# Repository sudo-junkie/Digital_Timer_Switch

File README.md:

# Digital_Timer_Switch

KiCad 7 design files (schematic, PCB, BOM, gerbers) for ATMEGA328P-based timer switch

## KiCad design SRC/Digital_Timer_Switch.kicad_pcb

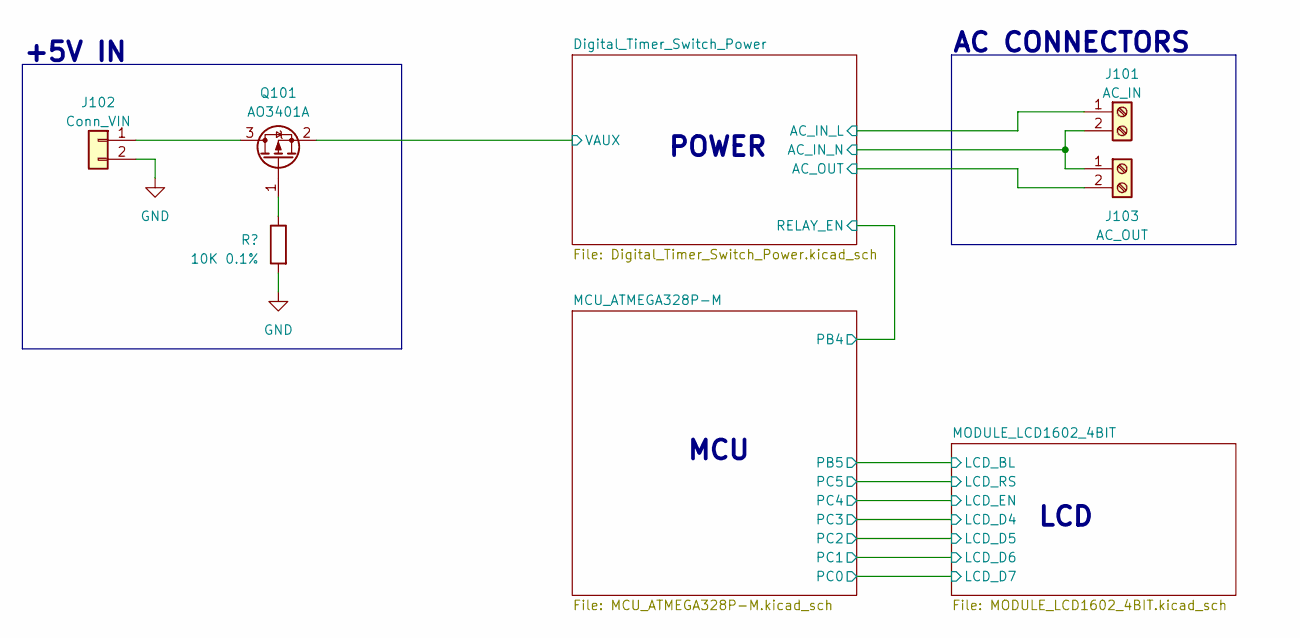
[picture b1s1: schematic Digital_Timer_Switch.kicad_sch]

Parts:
J101: AC_IN; TerminalBlock_Phoenix_MKDS-1,5-2-5.08_1x02_P5.08mm_Horizont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; MPN DB128V-5.08-2P-GN-S; LCSC PART# C2915639
J102: Conn_VIN; JST_XH_S2B-XH-A_1x02_P2.50mm_Horizontal; MPN S2B-XH-A-1(LF)(SN); LCSC PART# C163035
J103: AC_OUT; TerminalBlock_Phoenix_MKDS-1,5-2-5.08_1x02_P5.08mm_Horizont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; MPN DB128V-5.08-2P-GN-S; LCSC PART# C2915639
Q101: AO3401A; SOT-23; MPN AO3401; LCSC PART# C727156
R101: 10K 0.1%; R_0603_1608Metric; MPN RT0603BRD0710KL; LCSC PART# C95204

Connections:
/Digital_Timer_Switch_Power/AC_IN_L: J101.1; also elsewhere on the board
/Digital_Timer_Switch_Power/AC_IN_N: J101.2, J103.1; also elsewhere on the board
/Digital_Timer_Switch_Power/AC_OUT: J103.2; also elsewhere on the board
/Digital_Timer_Switch_Power/VAUX: Q101.2 (S); also elsewhere on the board
GND: J102.2, R101.2; also elsewhere on the board
unnamed: J102.1, Q101.3 (D)
unnamed: Q101.1 (G), R101.1

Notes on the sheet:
POWER
AC CONNECTORS
LCD
+5V IN
MCU

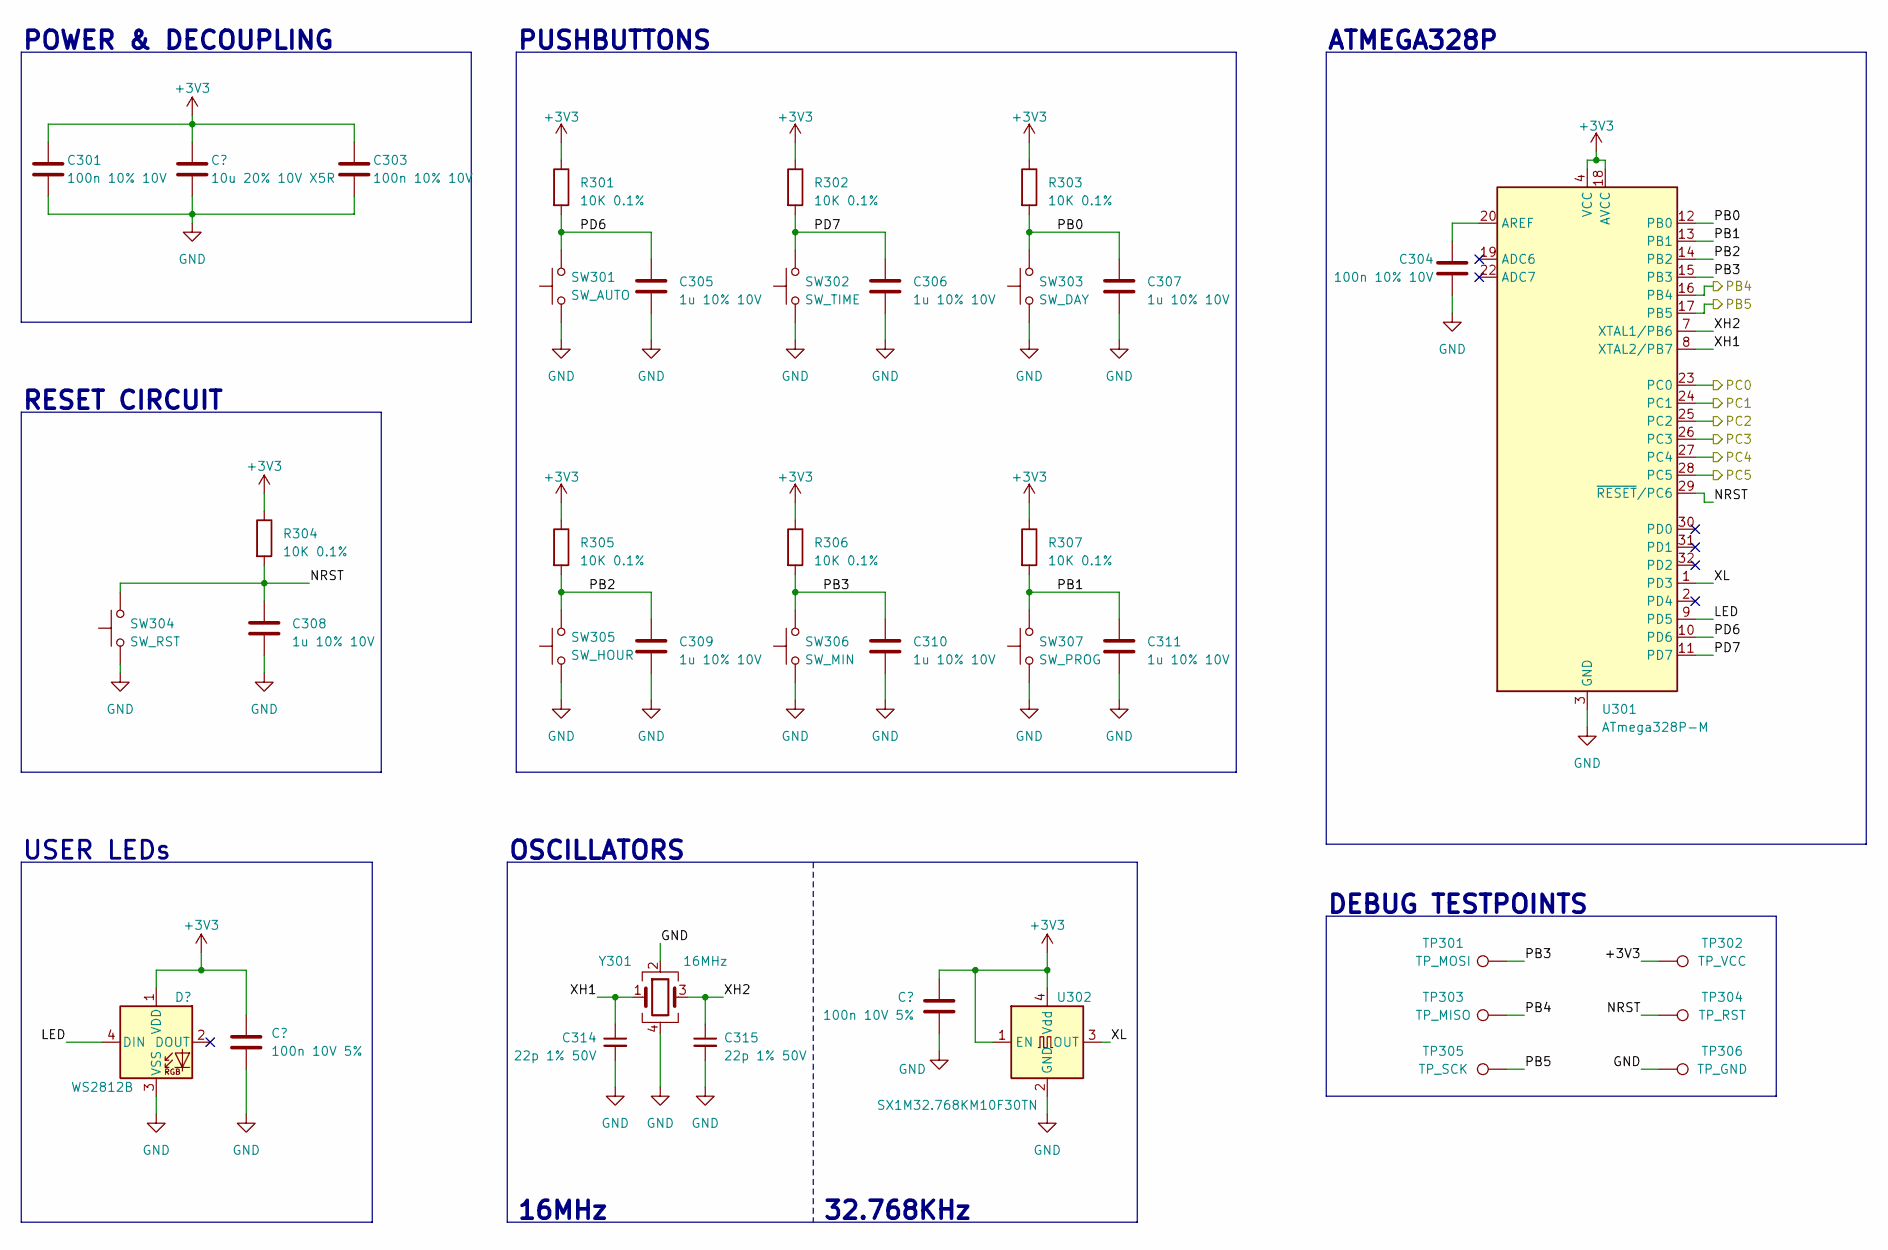
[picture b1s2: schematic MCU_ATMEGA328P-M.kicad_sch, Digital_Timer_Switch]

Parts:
C301, C303, C304: 100n 10% 10V; C_0603_1608Metric; MPN CC0603KRX7R6BB104; LCSC PART# C519438
C302: 10u 20% 10V X5R; C_0402_1005Metric; MPN CL05A106MP5NUNC; LCSC PART# C315248
C305, C306, C307, C308, C309, C310, C311: 1u 10% 10V; C_0603_1608Metric; MPN CC0603KRX7R6BB105; LCSC PART# C113807
C312, C313: 100n 10V 5%; C_0402_1005Metric; MPN CC0402JRX7R6BB104; LCSC PART# C527001
C314, C315: 22p 1% 50V; C_0603_1608Metric; MPN CC0603FRNPO9BN220; LCSC PART# C326840
D301: WS2812B; LED_WS2812B-2020_PLCC4_2.0x2.0mm; MPN XL-2020RGBC-WS2812B; LCSC PART# C5349955
R301, R302, R303, R304, R305, R306, R307: 10K 0.1%; R_0603_1608Metric; MPN RT0603BRD0710KL; LCSC PART# C95204
SW301: SW_AUTO; SW_SPST_Omron_B3FS-105xP; MPN TS-1095TS-B2C2-D2; LCSC PART# C5148360
SW302: SW_TIME; SW_SPST_Omron_B3FS-105xP; MPN TS-1095TS-B2C2-D2; LCSC PART# C5148360
SW303: SW_DAY; SW_SPST_Omron_B3FS-105xP; MPN TS-1095TS-B2C2-D2; LCSC PART# C5148360
SW304: SW_RST; SW_SPST_B3U-1000P; MPN B3U-1000P; LCSC PART# C231329
SW305: SW_HOUR; SW_SPST_Omron_B3FS-105xP; MPN TS-1095TS-B2C2-D2; LCSC PART# C5148360
SW306: SW_MIN; SW_SPST_Omron_B3FS-105xP; MPN TS-1095TS-B2C2-D2; LCSC PART# C5148360
SW307: SW_PROG; SW_SPST_Omron_B3FS-105xP; MPN TS-1095TS-B2C2-D2; LCSC PART# C5148360
TP301: TP_MOSI; TestPoint_Pad_D1.5mm
TP302: TP_VCC; TestPoint_Pad_D1.5mm
TP303: TP_MISO; TestPoint_Pad_D1.5mm
TP304: TP_RST; TestPoint_Pad_D1.5mm
TP305: TP_SCK; TestPoint_Pad_D1.5mm
TP306: TP_GND; TestPoint_Pad_D1.5mm
U301: ATmega328P-M; QFN-32-1EP_5x5mm_P0.5mm_EP3.1x3.1mm; MPN ATMEGA328P-MUR; LCSC PART# C2651951
U302: SX1M32.768KM10F30TN; Crystal_SMD_2016-4Pin_2.0x1.6mm; MPN SX1M32.768KM10F30TNN; LCSC PART# C2901615
Y301: 16MHz; Crystal_SMD_2016-4Pin_2.0x1.6mm; MPN TJ2116000UYGBC; LCSC PART# C2149179

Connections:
+3V3: C301.1, C302.1, C303.1, C312.1, C313.1, D301.1 (VDD), R301.1, R302.1, R303.1, R304.1, R305.1, R306.1, R307.1, TP302.1, U301.4 (VCC), U301.6 (VCC), U301.18 (AVCC), U302.1 (EN), U302.4 (Vdd); also elsewhere on the board
/MCU_ATMEGA328P-M/LED: D301.4 (DIN), U301.9 (PD5)
/MCU_ATMEGA328P-M/NRST: C308.1, R304.2, SW304.2, TP304.1, U301.29 (~RESET/PC6)
/MCU_ATMEGA328P-M/PB0: C307.1, R303.2, SW303.2, U301.12 (PB0)
/MCU_ATMEGA328P-M/PB1: C311.1, R307.2, SW307.2, U301.13 (PB1)
/MCU_ATMEGA328P-M/PB2: C309.1, R305.2, SW305.2, U301.14 (PB2)
/MCU_ATMEGA328P-M/PB3: C310.1, R306.2, SW306.2, TP301.1, U301.15 (PB3)
/MCU_ATMEGA328P-M/PB4: TP303.1, U301.16 (PB4); also elsewhere on the board
/MCU_ATMEGA328P-M/PB5: TP305.1, U301.17 (PB5); also elsewhere on the board
/MCU_ATMEGA328P-M/PC0: U301.23 (PC0); also elsewhere on the board
/MCU_ATMEGA328P-M/PC1: U301.24 (PC1); also elsewhere on the board
/MCU_ATMEGA328P-M/PC2: U301.25 (PC2); also elsewhere on the board
/MCU_ATMEGA328P-M/PC3: U301.26 (PC3); also elsewhere on the board
/MCU_ATMEGA328P-M/PC4: U301.27 (PC4); also elsewhere on the board
/MCU_ATMEGA328P-M/PC5: U301.28 (PC5); also elsewhere on the board
/MCU_ATMEGA328P-M/PD6: C305.1, R301.2, SW301.2, U301.10 (PD6)
/MCU_ATMEGA328P-M/PD7: C306.1, R302.2, SW302.2, U301.11 (PD7)
/MCU_ATMEGA328P-M/XH1: C314.1, U301.8 (XTAL2/PB7), Y301.1
/MCU_ATMEGA328P-M/XH2: C315.1, U301.7 (XTAL1/PB6), Y301.3
/MCU_ATMEGA328P-M/XL: U301.1 (PD3), U302.3 (OUT)
GND: C301.2, C302.2, C303.2, C304.2, C305.2, C306.2, C307.2, C308.2, C309.2, C310.2, C311.2, C312.2, C313.2, C314.2, C315.2, D301.3 (VSS), SW301.1, SW302.1, SW303.1, SW304.1, SW305.1, SW306.1, SW307.1, TP306.1, U301.3 (GND), U301.5 (GND), U301.21 (GND), U301.33 (GND), U302.2 (GND), Y301.2, Y301.4; also elsewhere on the board
unnamed: C304.1, U301.20 (AREF)

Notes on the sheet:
32.768KHz
ATMEGA328P
PUSHBUTTONS
16MHz
RESET CIRCUIT
OSCILLATORS
USER LEDs
POWER & DECOUPLING
DEBUG TESTPOINTS

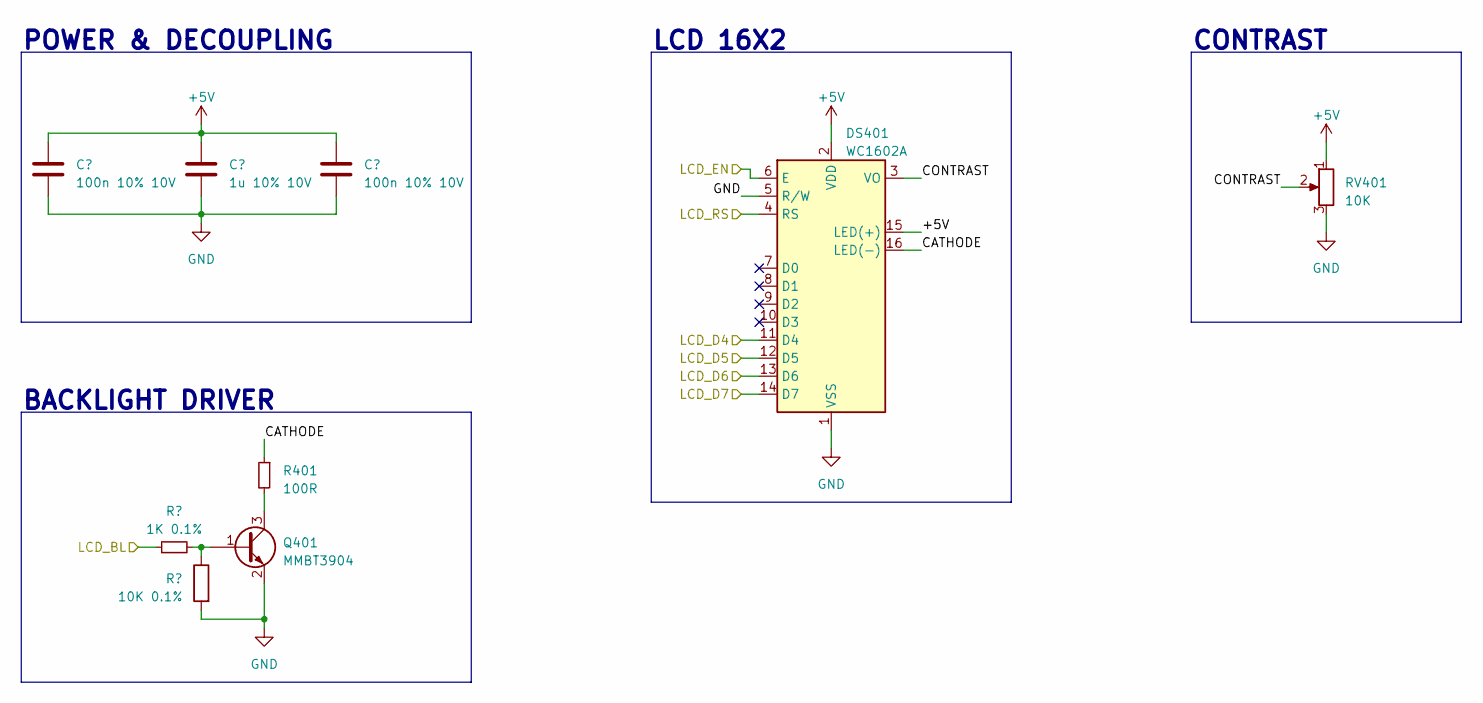
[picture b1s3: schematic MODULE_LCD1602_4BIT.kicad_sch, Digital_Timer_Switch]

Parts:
C401, C403: 100n 10% 10V; C_0603_1608Metric; MPN CC0603KRX7R6BB104; LCSC PART# C519438
C402: 1u 10% 10V; C_0603_1608Metric; MPN CC0603KRX7R6BB105; LCSC PART# C113807
DS401: WC1602A
Q401: MMBT3904; SOT-23; MPN MMBT3904; LCSC PART# C84104
R401: 100R; R_0603_1608Metric; MPN RC0603FR-07100RL; LCSC PART# C105588
R402: 1K 0.1%; R_0402_1005Metric; MPN ARG02BTC1001; LCSC PART# C2984405
R403: 10K 0.1%; R_0603_1608Metric; MPN RT0603BRD0710KL; LCSC PART# C95204
RV401: 10K; Potentiometer_Bourns_3314J_Vertical; MPN 3314J-1-103E; LCSC PART# C36376

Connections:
+5V: C401.1, C402.1, C403.1, DS401.2 (VDD), DS401.15 (LED(+)), RV401.1; also elsewhere on the board
/MCU_ATMEGA328P-M/PB5: R402.1; also elsewhere on the board
/MCU_ATMEGA328P-M/PC0: DS401.14 (D7); also elsewhere on the board
/MCU_ATMEGA328P-M/PC1: DS401.13 (D6); also elsewhere on the board
/MCU_ATMEGA328P-M/PC2: DS401.12 (D5); also elsewhere on the board
/MCU_ATMEGA328P-M/PC3: DS401.11 (D4); also elsewhere on the board
/MCU_ATMEGA328P-M/PC4: DS401.6 (E); also elsewhere on the board
/MCU_ATMEGA328P-M/PC5: DS401.4 (RS); also elsewhere on the board
/MODULE_LCD1602_4BIT/CATHODE: DS401.16 (LED(-)), R401.1
/MODULE_LCD1602_4BIT/CONTRAST: DS401.3 (VO), RV401.2
GND: C401.2, C402.2, C403.2, DS401.1 (VSS), DS401.5 (R/W), Q401.2 (E), R403.2, RV401.3; also elsewhere on the board
unnamed: Q401.1 (B), R402.2, R403.1
unnamed: Q401.3 (C), R401.2

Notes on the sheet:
POWER & DECOUPLING
CONTRAST
BACKLIGHT DRIVER
LCD 16X2

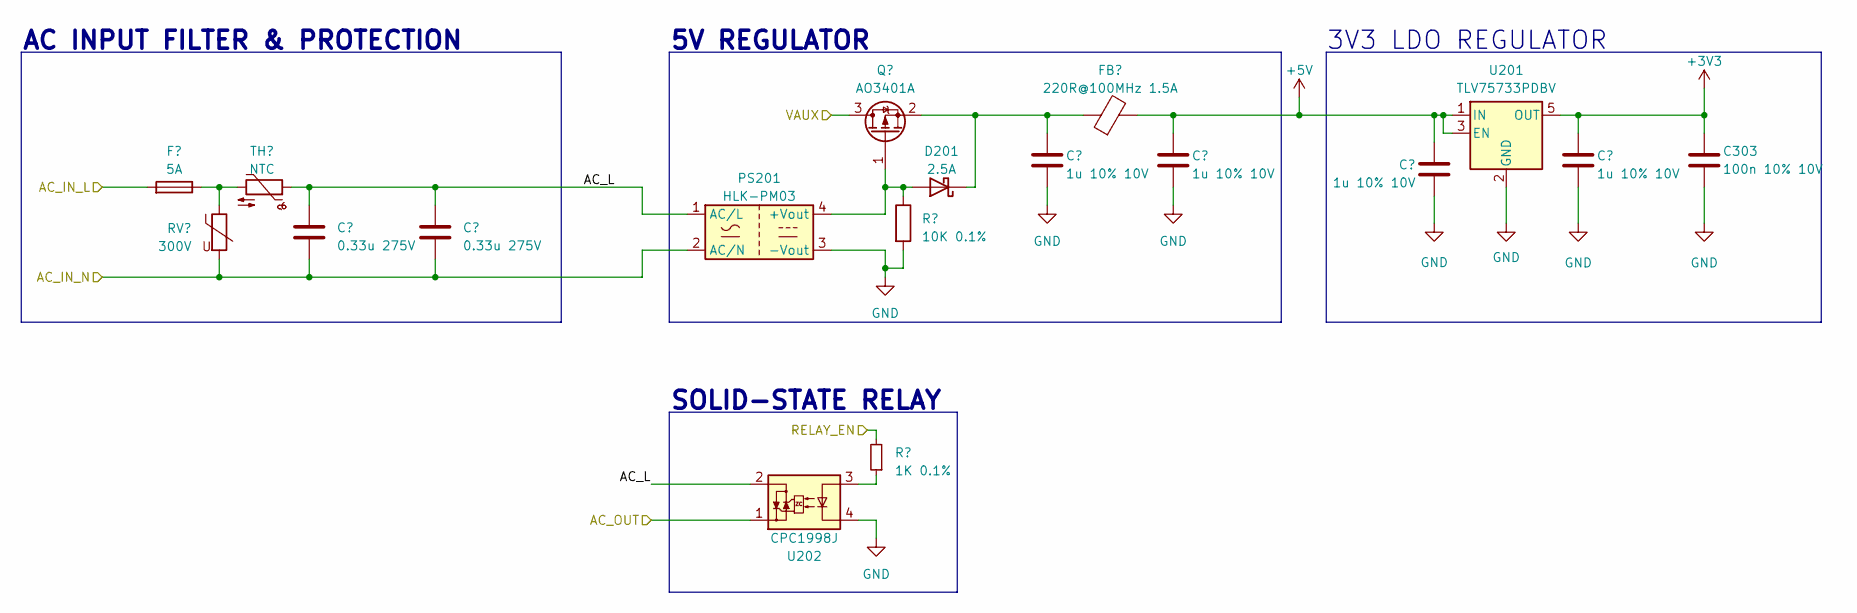
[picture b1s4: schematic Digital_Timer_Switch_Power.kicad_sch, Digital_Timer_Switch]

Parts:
C201, C202, C203, C205: 1u 10% 10V; C_0603_1608Metric; MPN CC0603KRX7R6BB105; LCSC PART# C113807
C206, C207: 0.33u 275V; C_Rect_L10.0mm_W3.0mm_P7.50mm_MKS4; MPN MPX334K31D3KN15800; LCSC PART# C504199
C303: 100n 10% 10V; C_0603_1608Metric; MPN CC0603KRX7R6BB104; LCSC PART# C519438
D201: 2.5A; D_SOD-323F; MPN PMEG2020EJ,115; LCSC PART# C841776
F201: 5A; Fuse_Littelfuse_395Series; MPN 40015000000; LCSC PART# C178828
FB201: 220R@100MHz 1.5A; L_0603_1608Metric; MPN HPZ1608D221-1R5TF; LCSC PART# C279803
MOV201: 300V; RV_Disc_D15.5mm_W5mm_P7.5mm; MPN VDR-14D301K; LCSC PART# C283948
PS201: HLK-PM03; Converter_ACDC_HiLink_HLK-PMxx; MPN HLK-PM03; LCSC PART# C209904
Q201: AO3401A; SOT-23; MPN AO3401; LCSC PART# C727156
R201: 10K 0.1%; R_0603_1608Metric; MPN RT0603BRD0710KL; LCSC PART# C95204
R202: 1K 0.1%; R_0402_1005Metric; MPN ARG02BTC1001; LCSC PART# C2984405
TH201: NTC; Fuse_Littelfuse_395Series; MPN NTC 10D-11; LCSC PART# C6793813
U201: TLV75733PDBV; SOT-23-5; MPN TLV75733PDBVR; LCSC PART# C485517
U202: CPC1998J; MPN CPC1998J; LCSC PART# C1559467

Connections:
+3V3: C203.1, C303.1, U201.5 (OUT); also elsewhere on the board
+5V: C202.1, C205.1, FB201.2, U201.1 (IN), U201.3 (EN); also elsewhere on the board
/Digital_Timer_Switch_Power/AC_IN_L: F201.2; also elsewhere on the board
/Digital_Timer_Switch_Power/AC_IN_N: C206.2, C207.2, MOV201.2, PS201.2 (AC/N); also elsewhere on the board
/Digital_Timer_Switch_Power/AC_L: C206.1, C207.1, PS201.1 (AC/L), TH201.1, U202.2
/Digital_Timer_Switch_Power/AC_OUT: U202.1; also elsewhere on the board
/Digital_Timer_Switch_Power/VAUX: Q201.3 (D); also elsewhere on the board
/MCU_ATMEGA328P-M/PB4: R202.2; also elsewhere on the board
GND: C201.2, C202.2, C203.2, C205.2, C303.2, PS201.3 (-Vout), R201.2, U201.2 (GND), U202.4; also elsewhere on the board
unnamed: D201.2 (A), PS201.4 (+Vout), Q201.1 (G), R201.1
unnamed: C201.1, D201.1 (K), FB201.1, Q201.2 (S)
unnamed: F201.1, MOV201.1, TH201.2
unnamed: R202.1, U202.3

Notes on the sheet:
AC INPUT FILTER & PROTECTION
SOLID-STATE RELAY
3V3 LDO REGULATOR
5V REGULATOR

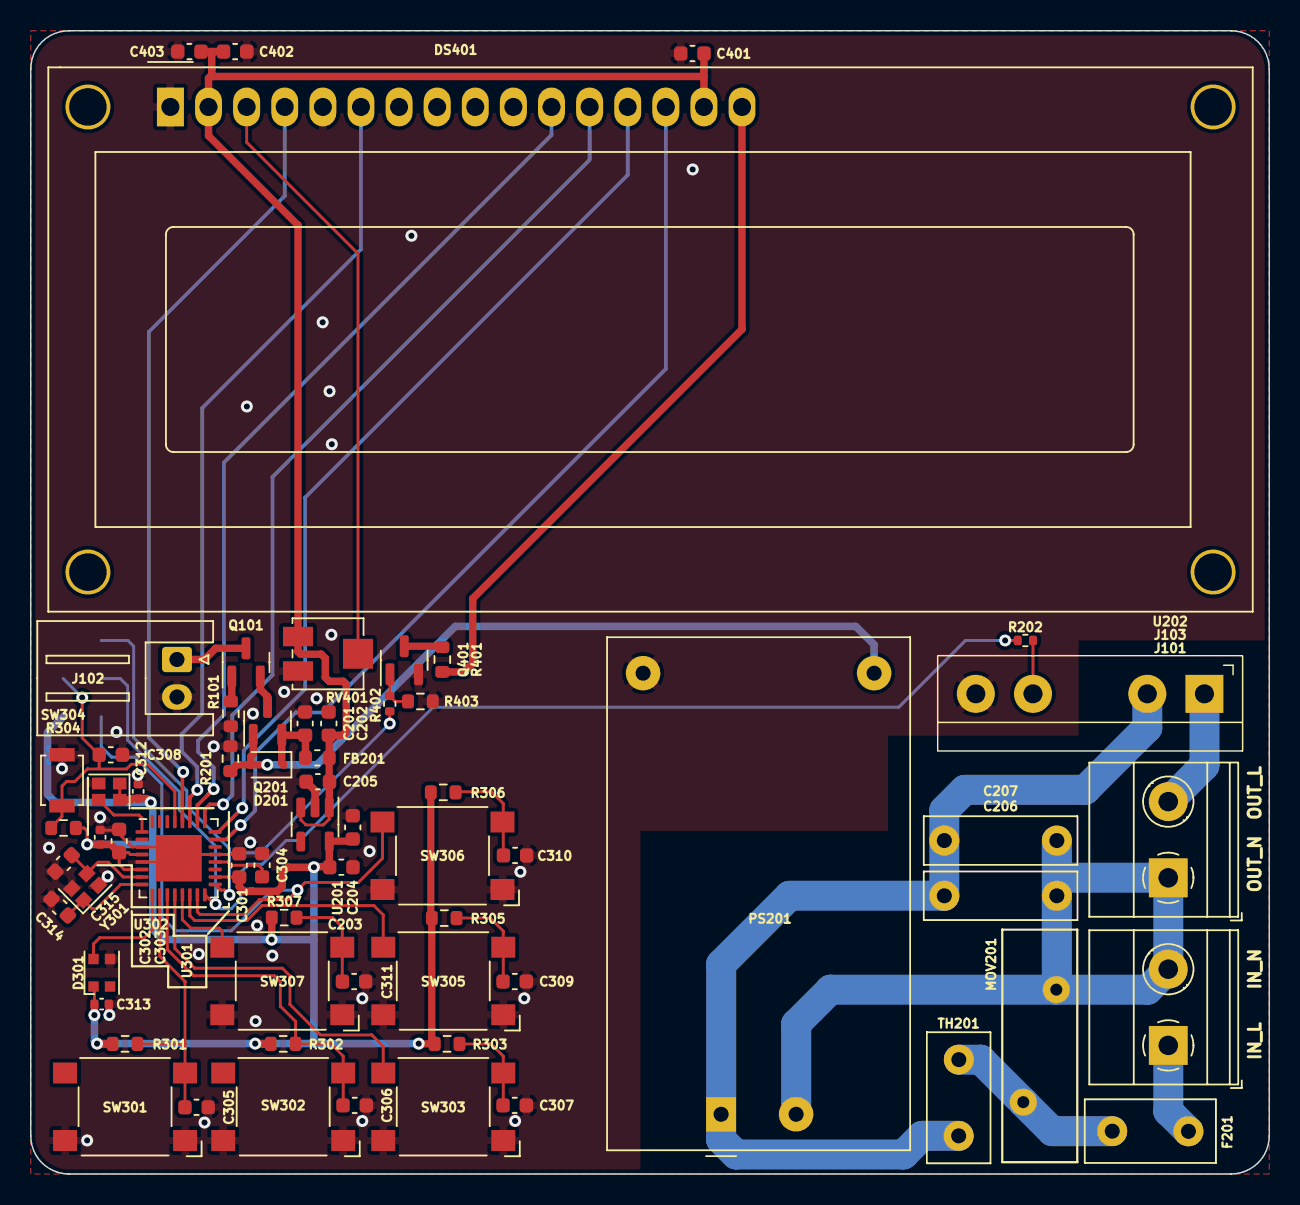
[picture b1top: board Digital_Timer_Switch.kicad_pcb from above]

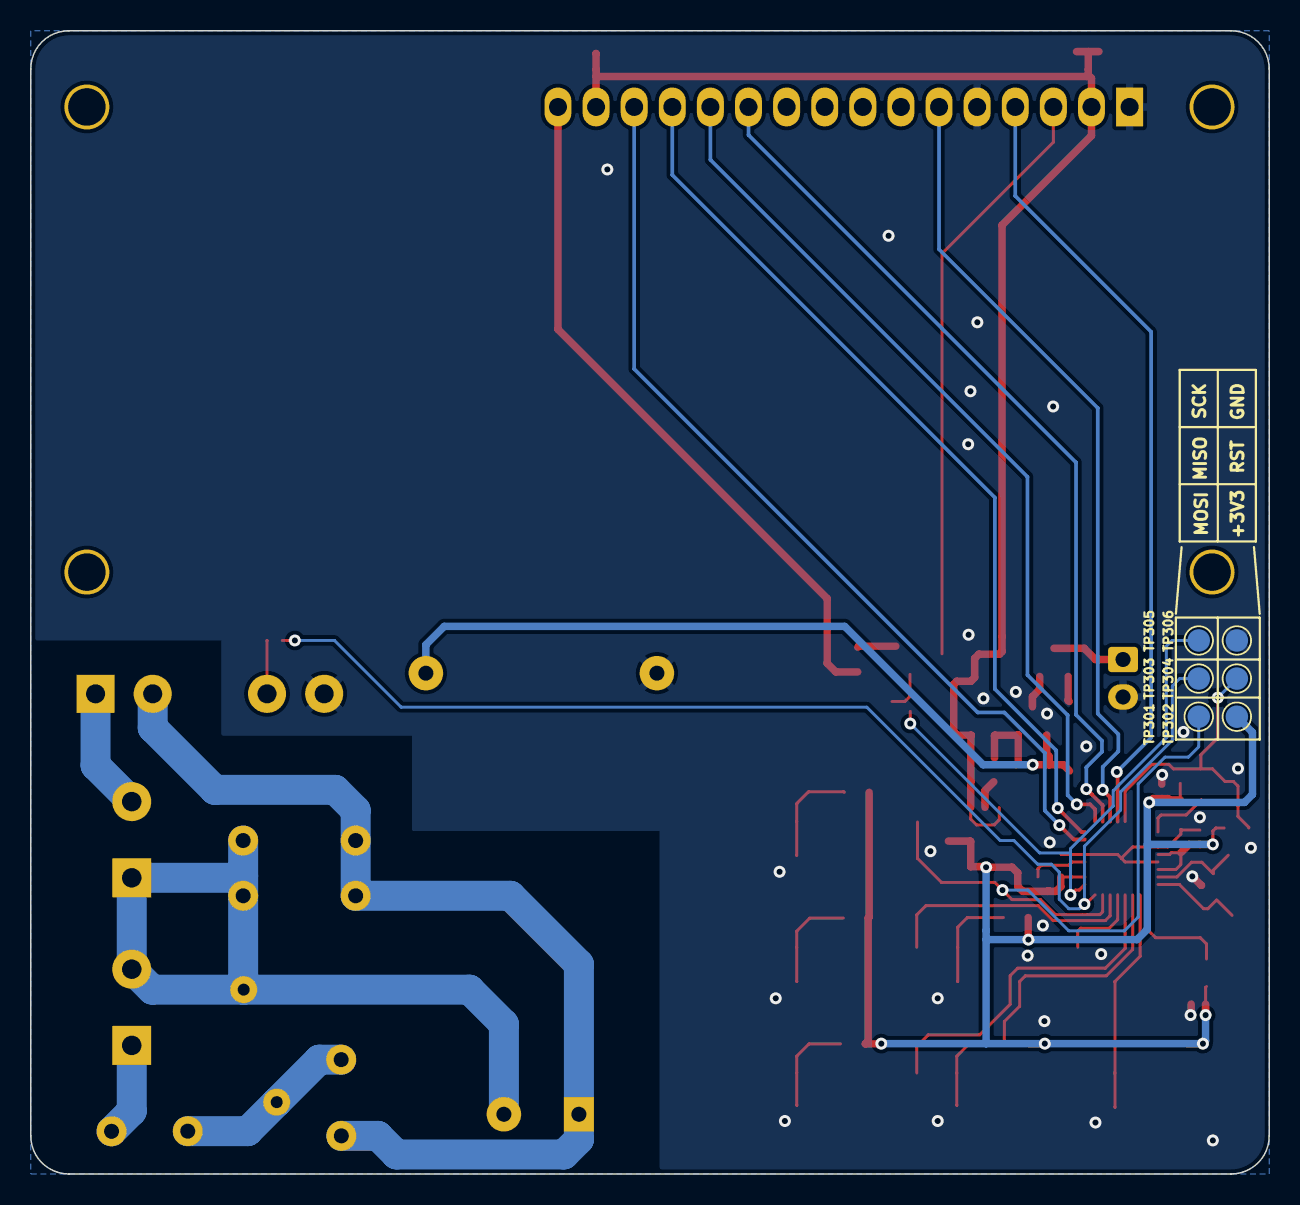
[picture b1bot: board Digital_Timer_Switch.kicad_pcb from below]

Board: 2 copper layers, 82.5 x 76.2 mm, 71 parts (6 on the bottom side), 38 nets.

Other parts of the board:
C204: 100n 10% 10V; C_0603_1608Metric

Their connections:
+3V3: C204.1; also elsewhere on the board
GND: C204.2; also elsewhere on the board

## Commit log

2023-08-02 Added debug testpoints.
